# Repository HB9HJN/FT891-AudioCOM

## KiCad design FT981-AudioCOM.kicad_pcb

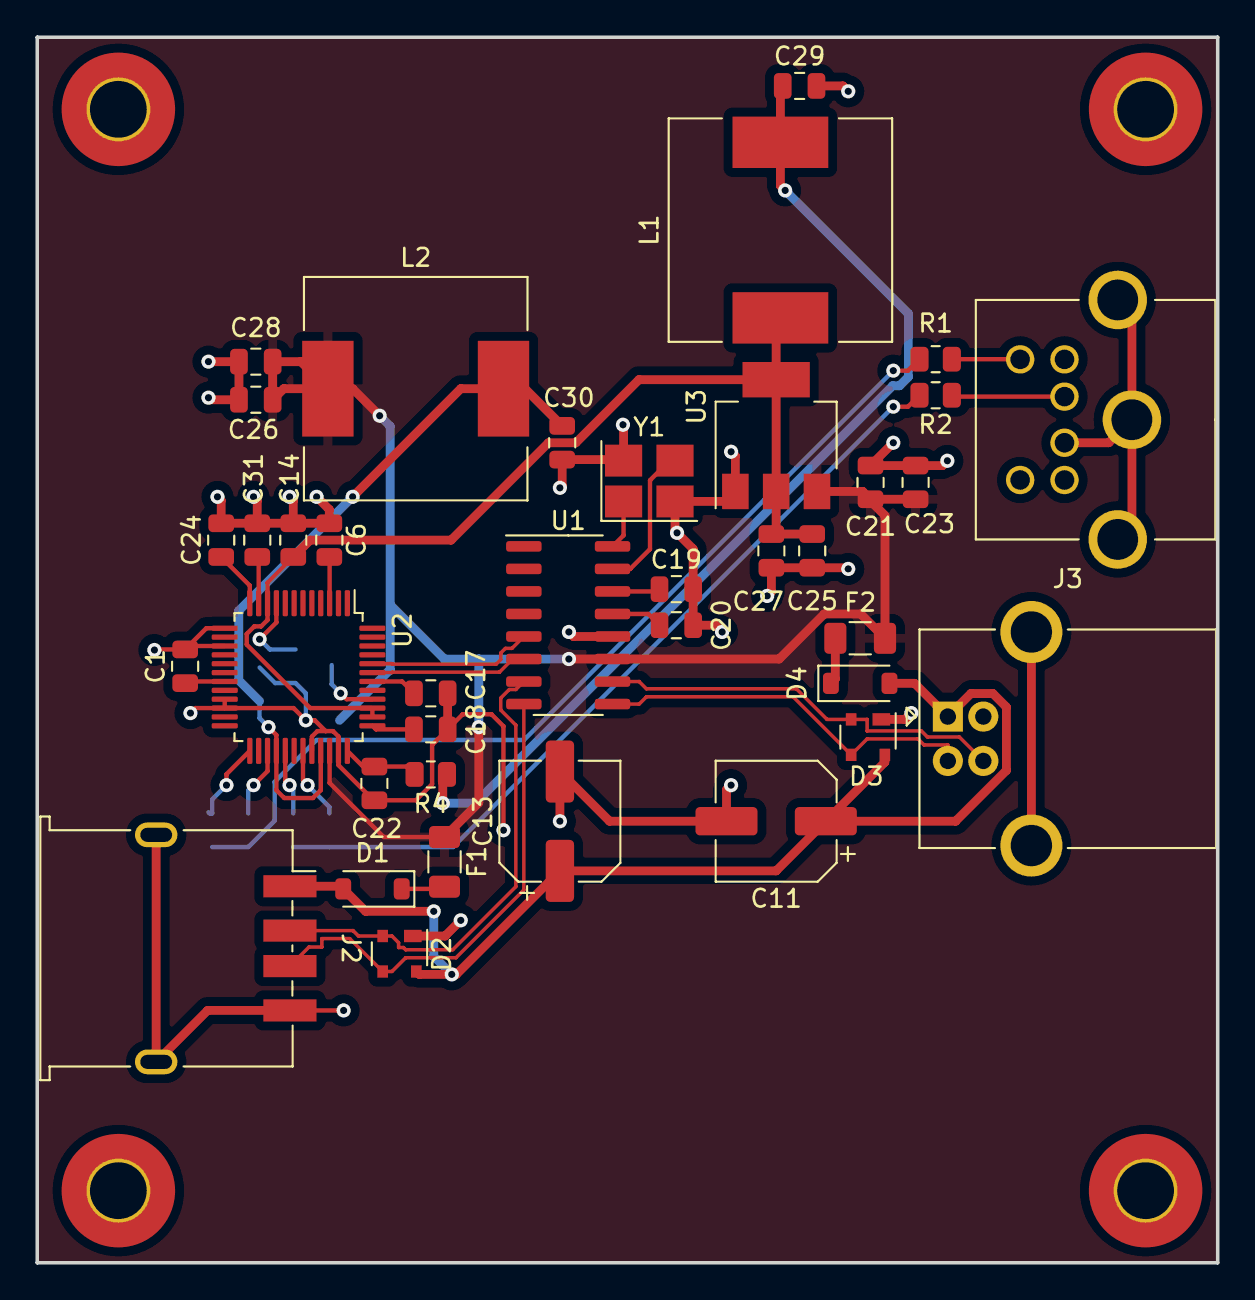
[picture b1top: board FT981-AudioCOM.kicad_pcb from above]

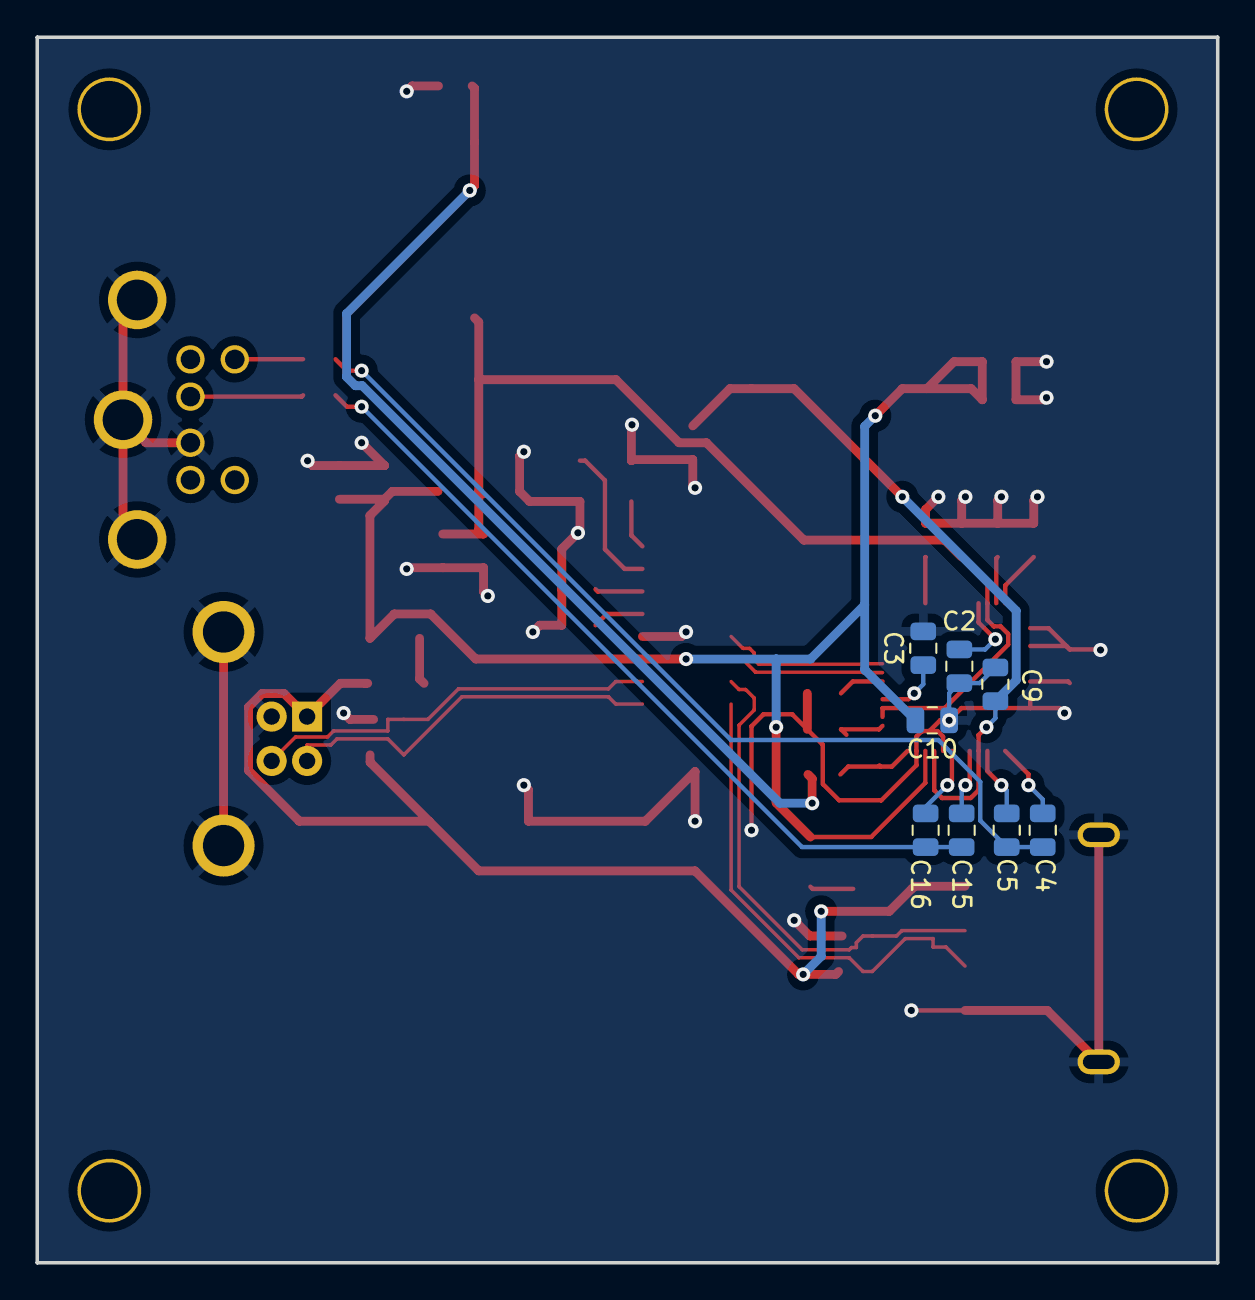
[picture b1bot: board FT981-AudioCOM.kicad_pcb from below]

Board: 2 copper layers, 66.5 x 69.1 mm, 50 parts (8 on the bottom side), 35 nets.

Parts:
C1, C2, C3, C6, C9, C10, C14, C23, C25, C26, C29, C30: 100nF; C_0805_2012Metric
C4, C5: 0.47uF; C_0805_2012Metric
C11, C13: 100uF; CP_Elec_6.3x5.4
C15, C16, C19, C20: 1uF; C_0805_2012Metric
C17, C18, C21, C22, C27, C28: 10uF; C_0805_2012Metric
C24, C31: 100n; C_0805_2012Metric
D1, D4: D_Schottky; D_SOD-123
D2, D3: PRTR5V0U2X; SOT-143
F1, F2: Polyfuse; Fuse_1206_3216Metric
H1, H2, H3, H4: MountingHole; MountingHole_3.2mm_M3_Pad_TopOnly
J1: Mini-DIN-6; MINI_DIN_6
J2: USB_A; USB_A_CONN_LCSC
J3: USB_B; USB_B_OST_USB-B1HSxx_Horizontal
L1, L2: 100uH; L_12x12mm_H8mm
R1, R2, R4: 0; R_0805_2012Metric
U1: SL2.1A; SOP-16_3.9x9.9mm_P1.27mm
U2: CM118B; LQFP-48_7x7mm_P0.5mm
U3: NCP1117-3.3_SOT223; SOT-223-3_TabPin2
Y1: 12MHz; Crystal_SMD_3225-4Pin_3.2x2.5mm_HandSoldering

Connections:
+3.3V: C14.1, C25.1, C27.1, L1.1, U2.10 (PWRSEL), U2.38 (MICONLY), U2.39 (MSEL), U3.2 (VO)
+3.3VA: C29.1, L1.2, R4.1
+5P: C11.1, C13.1, D1.2 (A), D2.4 (VCC), D3.4 (VCC), D4.2 (A), J2.1 (VBUS), J3.1 (VBUS)
+5V: C10.1, C21.1, C23.1, C26.1, C28.1, F1.1, F2.1, L2.1, U1.11 (VDD5), U2.34 (DVDD), U3.3 (VI)
+5VA: C9.1, C30.1, L2.2, U2.28 (AVDD), U2.33 (AVDD)
/DA+: D2.3 (I/O2), J2.3 (D+), U1.8 (DP1)
/DA-: D2.2 (I/O1), J2.2 (D-), U1.7 (DM1)
/DB+: D3.2 (I/O1), J3.3 (D+), U1.10 (DP)
/DB-: D3.3 (I/O2), J3.2 (D-), U1.9 (DM)
/DC+: U1.6 (DP2), U2.43 (USBDP)
/DC-: U1.5 (DM2), U2.44 (USBDM)
DAT_IN: C15.2, C16.2, R2.2
DAT_OUT: C4.1, C5.1, R1.2
GND: C1.2, C2.2, C3.2, C6.2, C9.2, C10.2, C11.2, C13.2, C14.2, C17.2, C18.2, C19.2, C20.2, C21.2, C22.2, C23.2, C24.2, C25.2, C26.2, C27.2, C28.2, C29.2, C30.2, C31.2, D2.1 (GND), D3.1 (GND), J1.2, J2.4 (GND), J2.5 (Shield), J3.4 (GND), J3.5 (Shield), U1.12 (GND), U2.13 (MODE), U2.15 (DVSS), U2.21 (TEST), U2.22 (AVSS), U2.32 (AVSS), U2.35 (DVSS), U3.1 (GND), Y1.2, Y1.4
unnamed: C17.1, U2.42 (DREG33)
unnamed: C18.1, U2.37 (DREG18)
unnamed: C24.1, U2.12 (DREG33)
unnamed: C31.1, U2.11 (DREG18)
unnamed: D1.1 (K), F1.2
unnamed: D4.1 (K), F2.2
unnamed: J1.1, R2.1
unnamed: J1.6, R1.1
unnamed: C19.1, U1.14 (VDD18)
unnamed: C20.1, U1.13 (VDD33)
unnamed: U1.16 (XIN), Y1.1
unnamed: U1.15 (XOUT), Y1.3
unnamed: C22.1, R4.2, U2.36 (AREG36)
unnamed: C15.1, U2.29 (LOL)
unnamed: C16.1, U2.31 (LOR)
unnamed: C4.2, U2.25 (MICINL)
unnamed: C5.2, U2.27 (MICINR)
unnamed: C1.1, U2.19 (MUTEP)
unnamed: C2.1, U2.9 (MUTER)
unnamed: C6.1, U2.3 (VOLDN)
unnamed: C3.1, U2.40 (VOLUP)

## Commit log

2023-10-04 upload init
2024-06-29 final
